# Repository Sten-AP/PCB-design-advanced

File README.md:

# PCB-design-advanced
## Ontwerpopdracht 1
Opdracht 1 is een horloge waarvan de tijd wordt weergeven met LED's. Het schema en de PCB zijn gemaakt in kicad.
De horloge bestaat voornamelijk uit 24 LED's, een ATTINY414 met bijhorende kristal, een spanningsregelaar om van 3V naar 5V te gaan, knoppen (met pullup), een mosfet voor de LED's uiten aan te schakelen, een programmeerheader (UDPI) en een knoopcelhouder.

Dit was een nieuwe manier was van het ontwerpen van een PCB omdat er nu een onderzoek gedaan moest worden. Het onderzoek van deze opdracht is niet zo goed, dit was de bedoeling van de lector om ons er van bewust te maken.

Omdat er een probleem was met de footprint van de LED's kon de eerste versie niet werken, de ATTINY programmeerde wel maar de LED's waren verkeerd. Er kon geen nieuwe meer besteld worden door tijdsgebrek dus heb ik geprobeerd om zo goed mogelijk de LED's 90 graden gedraait te monteren op een nieuwe PCB. Dit heeft gewerkt maar nu werd het programmeren een probleem. Wederom kon de ATTINY geprogrammeerd worden maar deze keer deden de LED's niet wat ik in de programmatie plaatste, deze begonnen allemaal random aan en uit te gaan. Aangezien meerdere dit probleem hadden werd er vanuitgegaan dat het probleem aan de ATTINY lag.

## Ontwerpopdracht 2
Opdracht 2 is een macropad. Ook dit schema en PCB zijn gemaakt in kicad.
De macropad bestaat voornamelijk uit 2 trimmers, 6 toetsenbordswitches en een raspberry pico W. Omdat de trimmers ingedrukt kunnen worden als knop wil dit zeggen dat er 8 knoppen zijn. Deze knoppen zijn geschakeld in een matrix en bevatten daarvoor ook de nodige diodes.

Aangezien ik nu bewust was van het nodige onderzoek heb ik een grote stap gemaakt hiermee.

Deze opdracht is volledig compleet en is verlopen zonder fouten.

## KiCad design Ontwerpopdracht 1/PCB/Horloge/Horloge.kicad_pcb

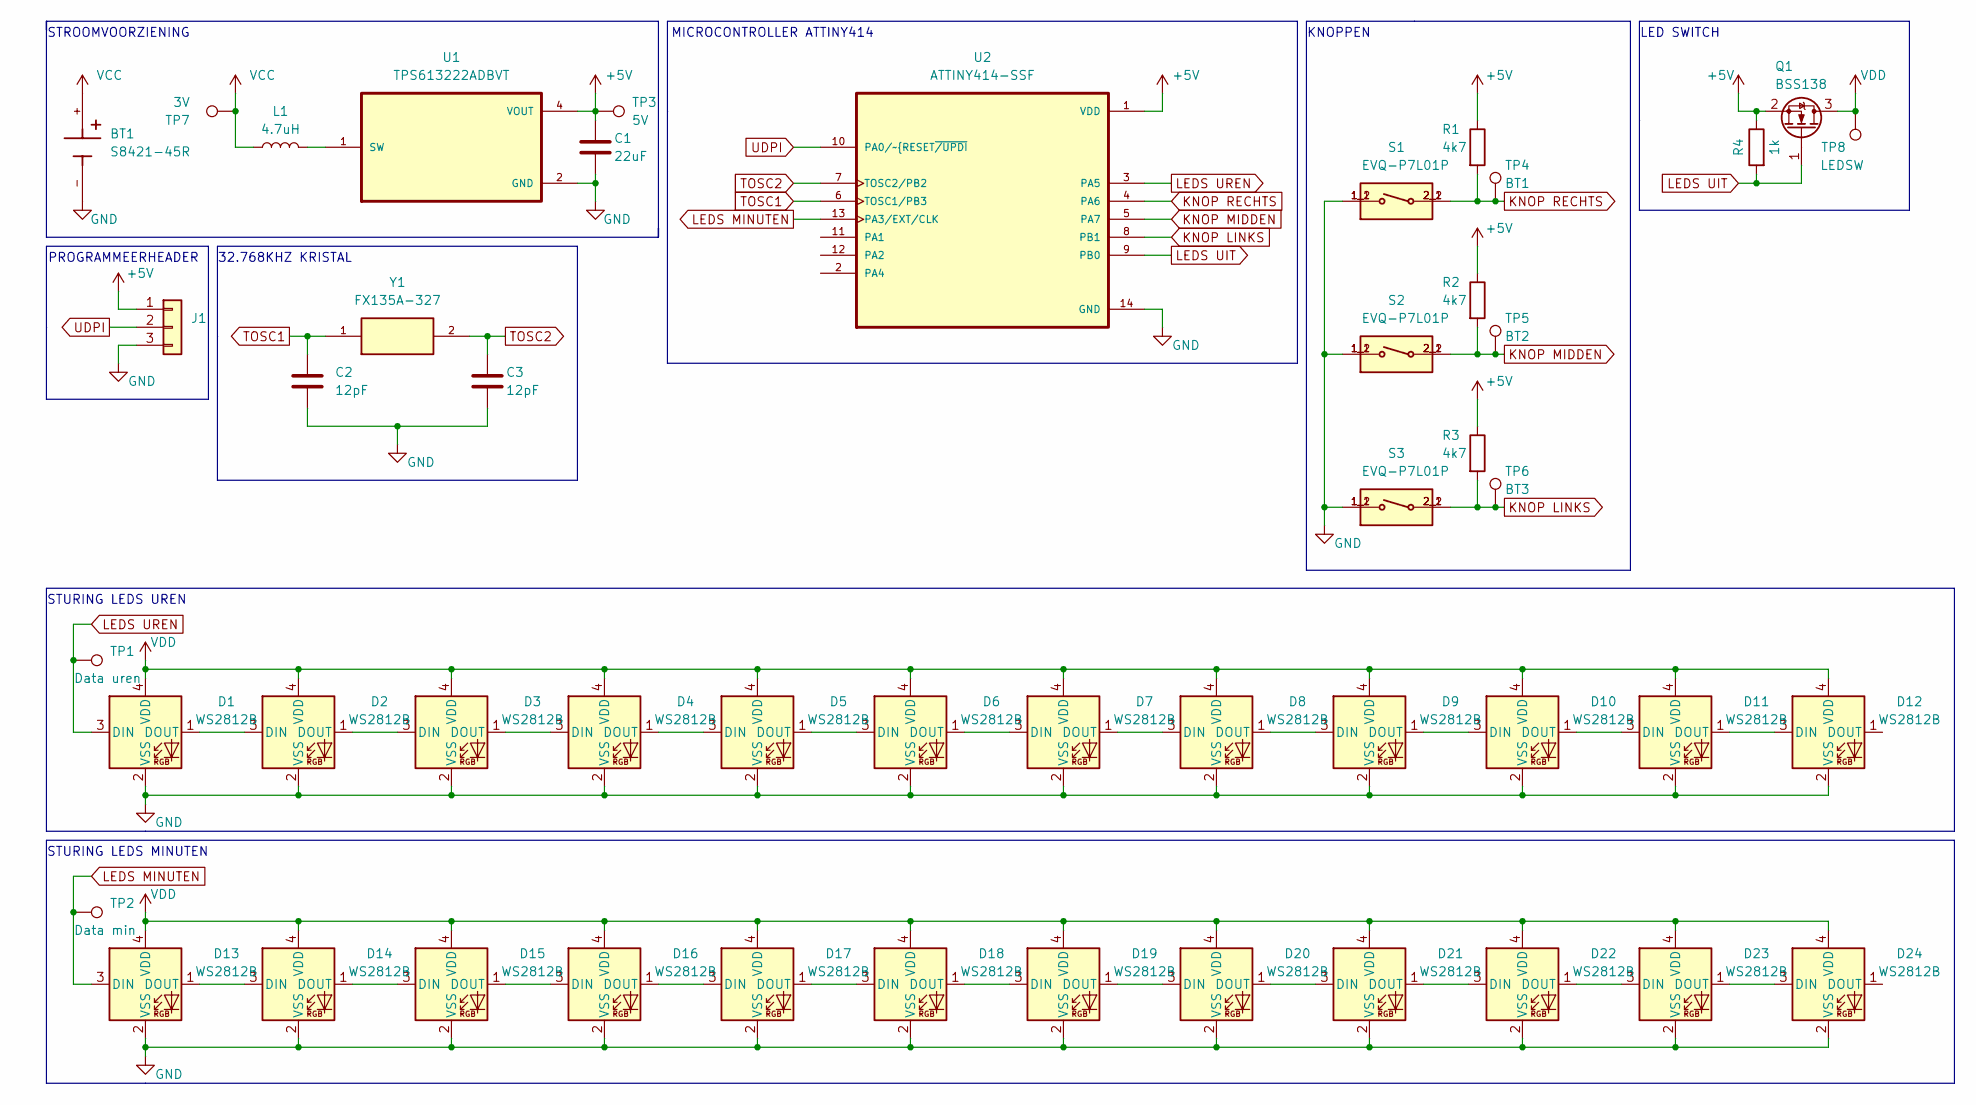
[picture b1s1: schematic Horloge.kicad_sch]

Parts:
BT1: S8421-45R; BAT_S8421-45R; PARTREV 5
C1: 22uF; C_0805_2012Metric_Pad1.18x1.45mm_HandSolder
C2, C3: 12pF; C_0805_2012Metric_Pad1.18x1.45mm_HandSolder
D1, D2, D3, D4, D5, D6, D7, D8, D9, D10, D11, D12, D13, D14, D15, D16, D17, D18, D19, D20, D21, D22, D23, D24: WS2812B; LED_WS2812B-2020_PLCC4_2.0x2.0mm
J1: Conn_01x03; PinHeader_1x03_P2.54mm_Vertical
L1: 4.7uH; L_Sunlord_SWPA5020S
Q1: BSS138; SOT-23
R1, R2, R3: 4k7; R_0805_2012Metric_Pad1.20x1.40mm_HandSolder
R4: 1k; R_0805_2012Metric_Pad1.20x1.40mm_HandSolder
S1, S2, S3: EVQ-P7L01P; SW_EVQ-P7L01P; PARTREV N/A
TP1: Data uren; TestPoint_Pad_1.5x1.5mm
TP2: Data min; TestPoint_Pad_1.5x1.5mm
TP3: 5V; TestPoint_Pad_1.5x1.5mm
TP4: BT1; TestPoint_Pad_1.5x1.5mm
TP5: BT2; TestPoint_Pad_1.5x1.5mm
TP6: BT3; TestPoint_Pad_1.5x1.5mm
TP7: 3V; TestPoint_Pad_1.5x1.5mm
TP8: LEDSW; TestPoint_Pad_1.5x1.5mm
U1: TPS613222ADBVT; SOT95P280X145-5N
U2: ATTINY414-SSF; SOIC127P600X175-14N
Y1: FX135A-327; OSCCC150X320X90-2N

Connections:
+5V: C1.1, J1.1, Q1.2 (S), R1.1, R2.1, R3.1, R4.1, TP3.1, U1.4 (VOUT), U2.1 (VDD)
GND: BT1.-, C1.2, C2.2, C3.2, D1.2 (VSS), D2.2 (VSS), D3.2 (VSS), D4.2 (VSS), D5.2 (VSS), D6.2 (VSS), D7.2 (VSS), D8.2 (VSS), D9.2 (VSS), D10.2 (VSS), D11.2 (VSS), D12.2 (VSS), D13.2 (VSS), D14.2 (VSS), D15.2 (VSS), D16.2 (VSS), D17.2 (VSS), D18.2 (VSS), D19.2 (VSS), D20.2 (VSS), D21.2 (VSS), D22.2 (VSS), D23.2 (VSS), D24.2 (VSS), J1.3, S1.1_1, S1.1_2, S2.1_1, S2.1_2, S3.1_1, S3.1_2, U1.2 (GND), U2.14 (GND)
KNOP LINKS: R3.2, S3.2_1, S3.2_2, TP6.1, U2.8 (PB1)
KNOP MIDDEN: R2.2, S2.2_1, S2.2_2, TP5.1, U2.5 (PA7)
KNOP RECHTS: R1.2, S1.2_1, S1.2_2, TP4.1, U2.4 (PA6)
LEDS MINUTEN: D13.3 (DIN), TP2.1, U2.13 (PA3/EXT/CLK)
LEDS UIT: Q1.1 (G), R4.2, U2.9 (PB0)
LEDS UREN: D1.3 (DIN), TP1.1, U2.3 (PA5)
unnamed: D1.1 (DOUT), D2.3 (DIN)
unnamed: D2.1 (DOUT), D3.3 (DIN)
unnamed: D3.1 (DOUT), D4.3 (DIN)
unnamed: D4.1 (DOUT), D5.3 (DIN)
unnamed: D5.1 (DOUT), D6.3 (DIN)
unnamed: D6.1 (DOUT), D7.3 (DIN)
unnamed: D7.1 (DOUT), D8.3 (DIN)
unnamed: D8.1 (DOUT), D9.3 (DIN)
unnamed: D9.1 (DOUT), D10.3 (DIN)
unnamed: D10.1 (DOUT), D11.3 (DIN)
unnamed: D11.1 (DOUT), D12.3 (DIN)
unnamed: D13.1 (DOUT), D14.3 (DIN)
unnamed: D14.1 (DOUT), D15.3 (DIN)
unnamed: D15.1 (DOUT), D16.3 (DIN)
unnamed: D16.1 (DOUT), D17.3 (DIN)
unnamed: D17.1 (DOUT), D18.3 (DIN)
unnamed: D18.1 (DOUT), D19.3 (DIN)
unnamed: D19.1 (DOUT), D20.3 (DIN)
unnamed: D20.1 (DOUT), D21.3 (DIN)
unnamed: D21.1 (DOUT), D22.3 (DIN)
unnamed: D22.1 (DOUT), D23.3 (DIN)
unnamed: D23.1 (DOUT), D24.3 (DIN)
unnamed: L1.2, U1.1 (SW)
TOSC1: C2.1, U2.6 (TOSC1/PB3), Y1.1
TOSC2: C3.1, U2.7 (TOSC2/PB2), Y1.2
UDPI: J1.2, U2.10 (PA0/~RESET~{/UPDI)
VCC: BT1.+, L1.1, TP7.1
VDD: D1.4 (VDD), D2.4 (VDD), D3.4 (VDD), D4.4 (VDD), D5.4 (VDD), D6.4 (VDD), D7.4 (VDD), D8.4 (VDD), D9.4 (VDD), D10.4 (VDD), D11.4 (VDD), D12.4 (VDD), D13.4 (VDD), D14.4 (VDD), D15.4 (VDD), D16.4 (VDD), D17.4 (VDD), D18.4 (VDD), D19.4 (VDD), D20.4 (VDD), D21.4 (VDD), D22.4 (VDD), D23.4 (VDD), D24.4 (VDD), Q1.3 (D), TP8.1

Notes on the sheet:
32.768KHZ KRISTAL
KNOPPEN
STURING LEDS UREN
STROOMVOORZIENING
LED SWITCH
PROGRAMMEERHEADER
STURING LEDS MINUTEN
MICROCONTROLLER ATTINY414

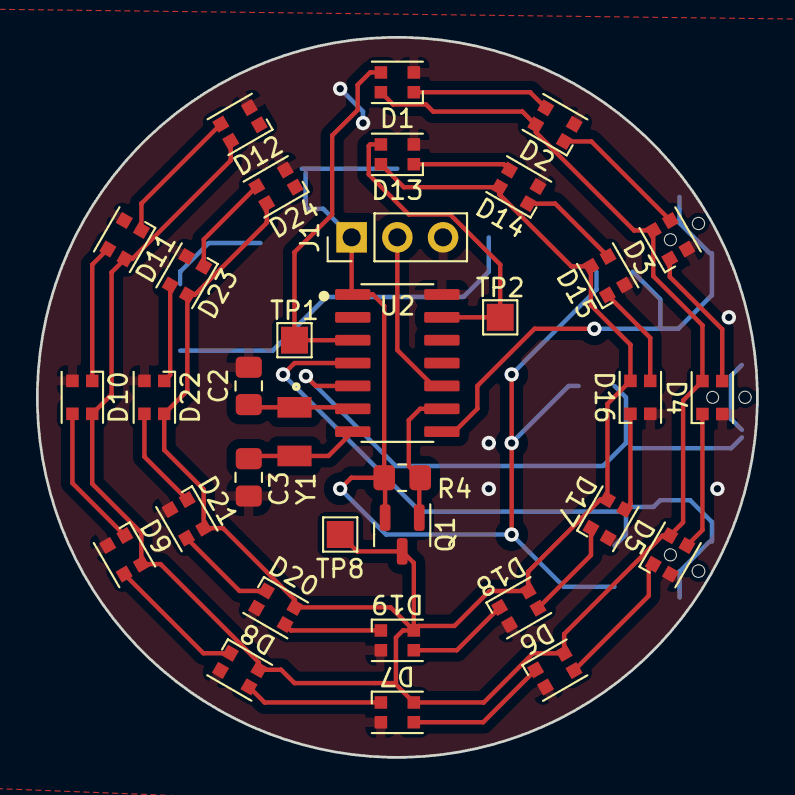
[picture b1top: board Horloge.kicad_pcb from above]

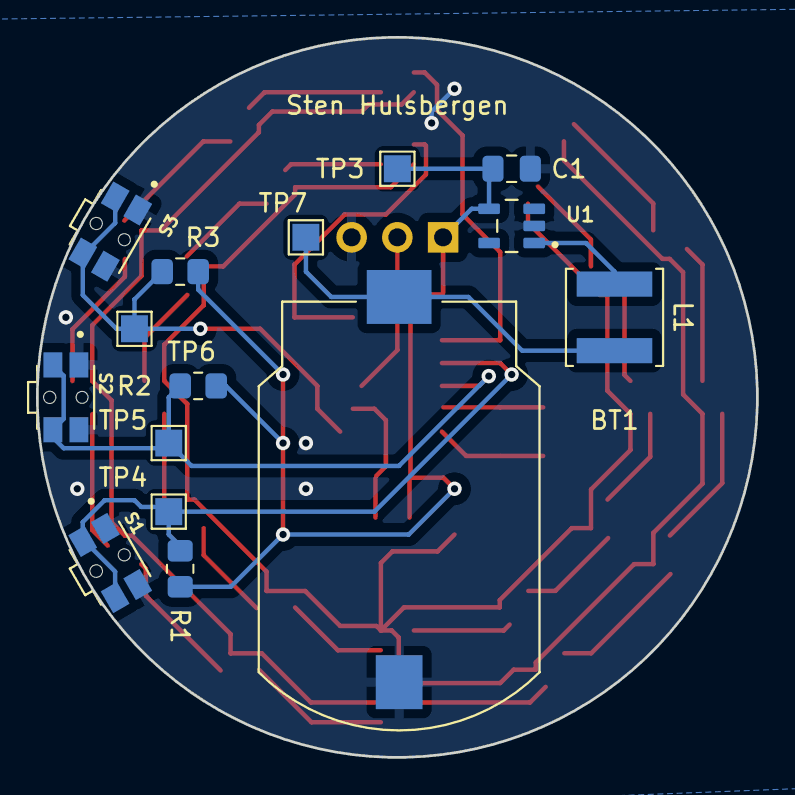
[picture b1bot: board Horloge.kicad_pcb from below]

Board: 2 copper layers, 40.0 x 40.0 mm, 49 parts (15 on the bottom side), 36 nets.

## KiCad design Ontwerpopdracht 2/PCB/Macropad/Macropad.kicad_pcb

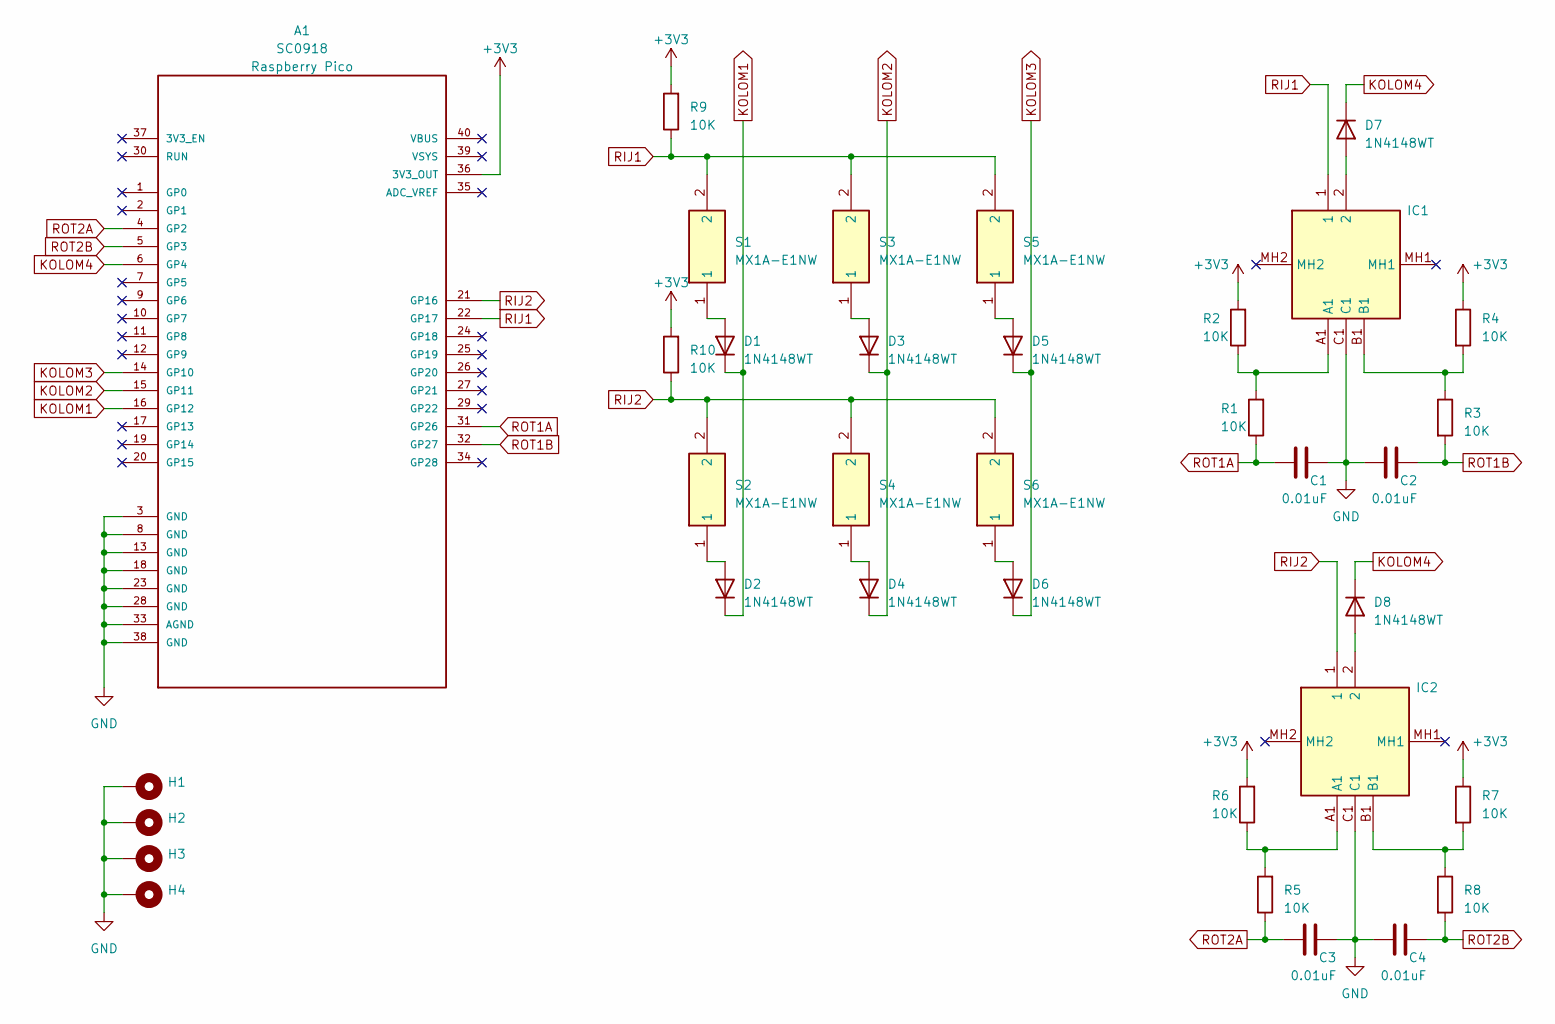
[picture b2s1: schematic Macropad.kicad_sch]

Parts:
A1: SC0918; MODULE_SC0918; PARTREV 1.6
C1, C2, C3, C4: 0.01uF; C_0805_2012Metric_Pad1.18x1.45mm_HandSolder
D1, D2, D3, D4, D5, D6, D7, D8: 1N4148WT; D_SOD-123
H1, H2, H3, H4: MountingHole_Pad; MountingHole_2.2mm_M2_Pad_Via
IC1, IC2: PEC12R-4220F-S0024; PEC12R4220FS0024; Mouser Part Number 652-PEC12R-4220F-S24
R1, R2, R3, R4, R5, R6, R7, R8, R9, R10: 10K; R_0805_2012Metric_Pad1.20x1.40mm_HandSolder
S1, S2, S3, S4, S5, S6: MX1A-E1NW; SW_Cherry_MX_1.00u_PCB; Mouser Part Number 540-MX1A-E1NW

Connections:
+3V3: A1.36 (3V3_OUT), R2.2, R4.1, R6.2, R7.1, R9.2, R10.2
GND: A1.3 (GND), A1.8 (GND), A1.13 (GND), A1.18 (GND), A1.23 (GND), A1.28 (GND), A1.33 (AGND), A1.38 (GND), C1.2, C2.1, C3.2, C4.1, H1.1, H2.1, H3.1, H4.1, IC1.C1, IC2.C1
KOLOM1: A1.16 (GP12), D1.1 (K), D2.1 (K)
KOLOM2: A1.15 (GP11), D3.1 (K), D4.1 (K)
KOLOM3: A1.14 (GP10), D5.1 (K), D6.1 (K)
KOLOM4: A1.6 (GP4), D7.1 (K), D8.1 (K)
unnamed: D1.2 (A), S1.1
unnamed: D2.2 (A), S2.1
unnamed: D3.2 (A), S3.1
unnamed: D4.2 (A), S4.1
unnamed: D5.2 (A), S5.1
unnamed: D6.2 (A), S6.1
unnamed: D7.2 (A), IC1.2
unnamed: D8.2 (A), IC2.2
unnamed: IC1.A1, R1.2, R2.1
unnamed: IC1.B1, R3.1, R4.2
unnamed: IC2.A1, R5.2, R6.1
unnamed: IC2.B1, R7.2, R8.1
RIJ1: A1.22 (GP17), IC1.1, R9.1, S1.2, S3.2, S5.2
RIJ2: A1.21 (GP16), IC2.1, R10.1, S2.2, S4.2, S6.2
ROT1A: A1.31 (GP26), C1.1, R1.1
ROT1B: A1.32 (GP27), C2.2, R3.2
ROT2A: A1.4 (GP2), C3.1, R5.1
ROT2B: A1.5 (GP3), C4.2, R8.2

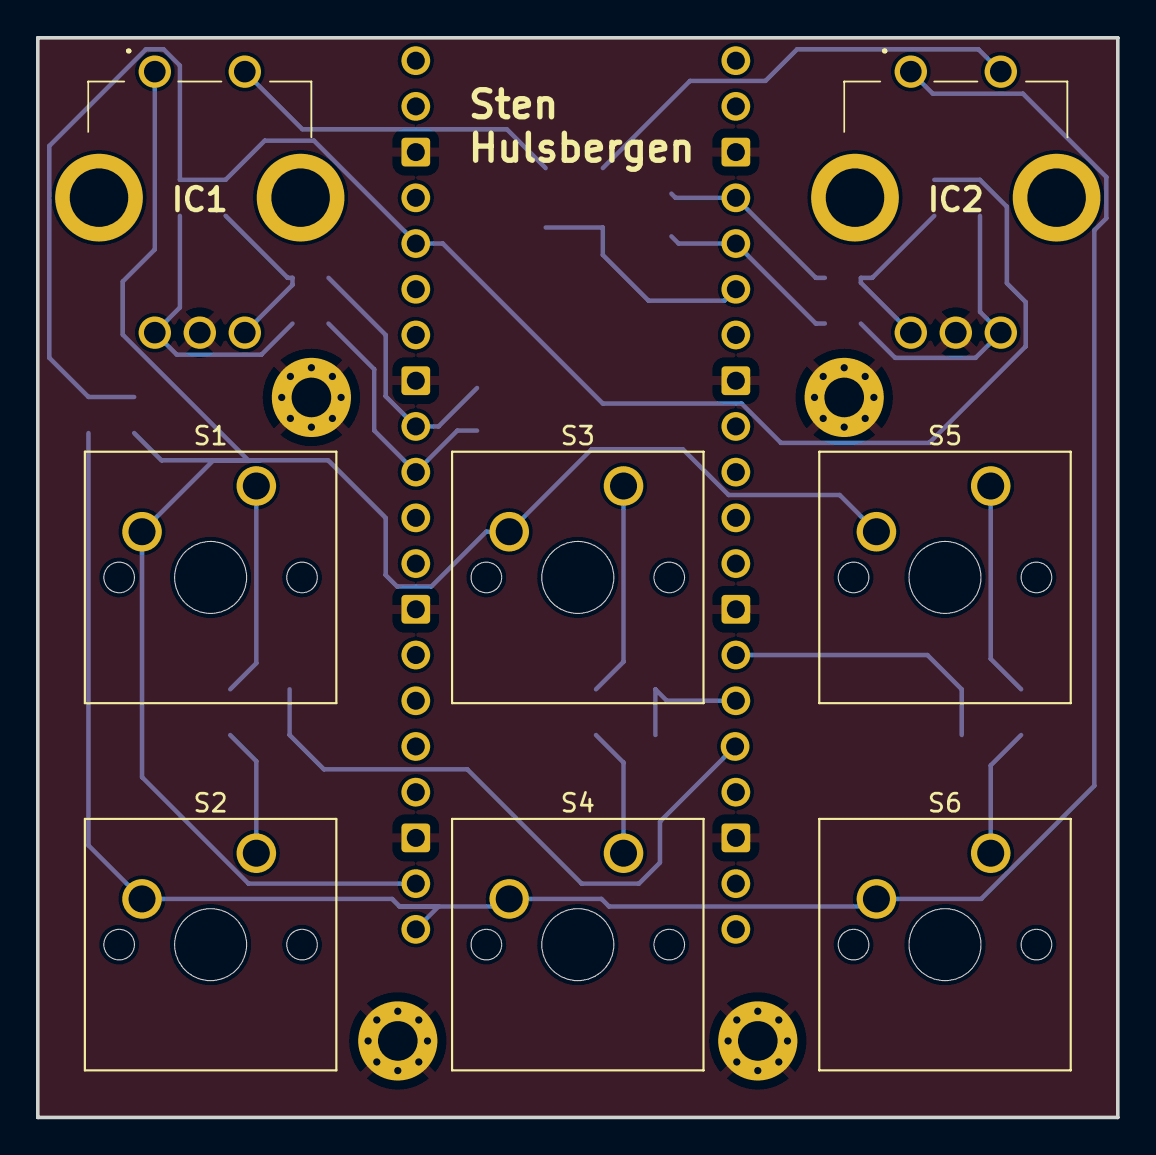
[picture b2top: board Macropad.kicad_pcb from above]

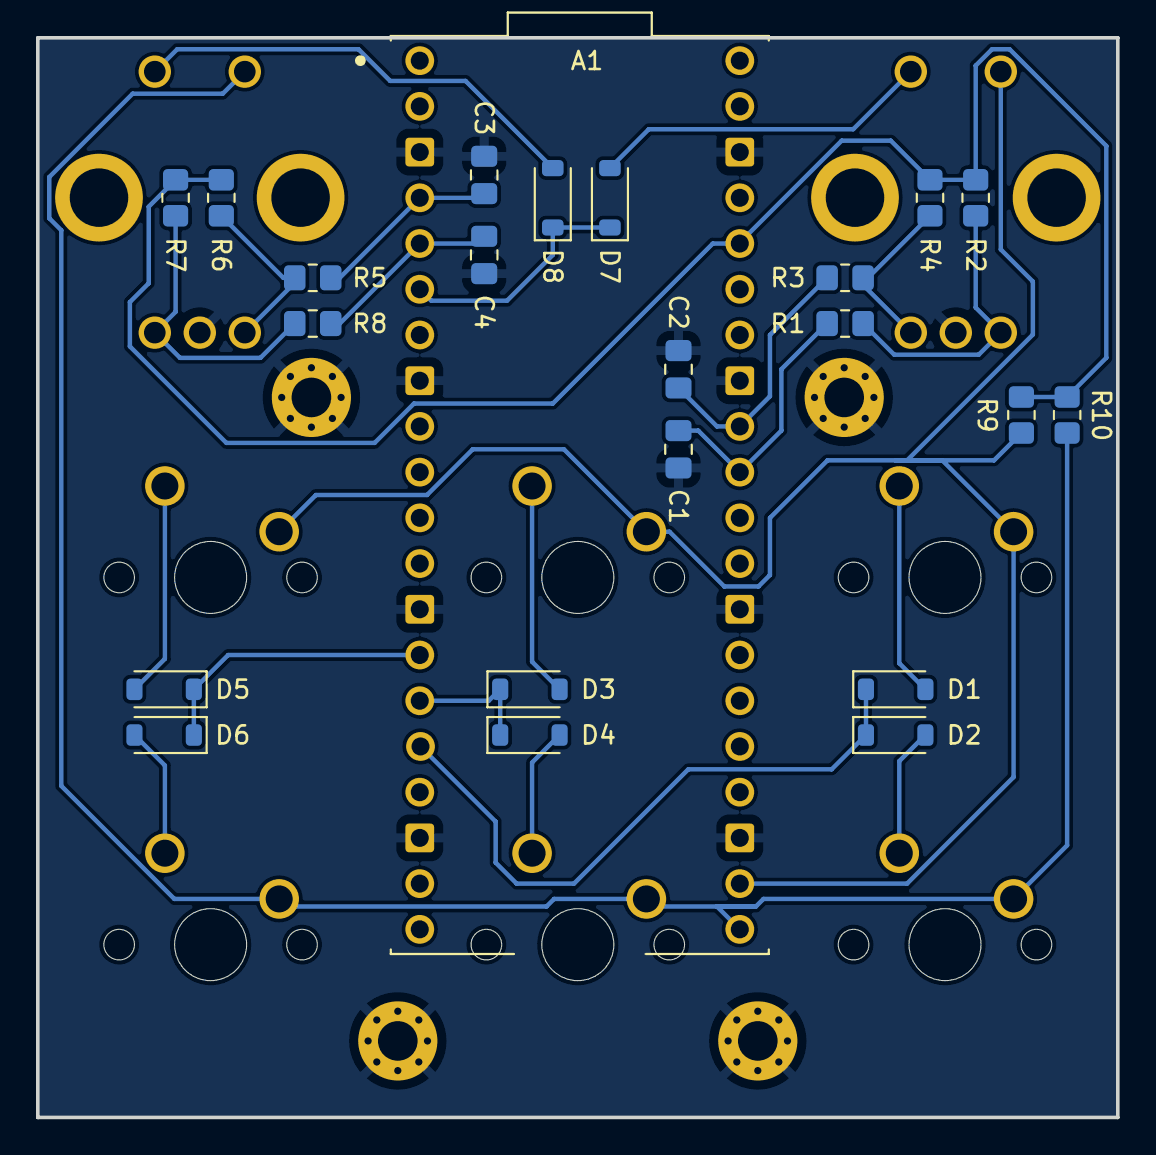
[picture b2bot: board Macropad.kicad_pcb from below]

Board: 2 copper layers, 60.0 x 60.0 mm, 35 parts (23 on the bottom side), 24 nets.

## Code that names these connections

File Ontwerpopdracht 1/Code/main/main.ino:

#include <tinyNeoPixel.h>

#define MOSFET PIN_PB0
#define LED_PIN_UREN PIN_PA5
#define LED_PIN_MINUTEN PIN_PA3
#define KNOP_RECHTS PIN_PA6
#define KNOP_MIDDEN PIN_PA7
#define KNOP_LINKS PIN_PB1

#define NUM_LEDS 12

tinyNeoPixel UREN(NUM_LEDS, LED_PIN_UREN, NEO_GRB);
tinyNeoPixel MINUTEN(NUM_LEDS, LED_PIN_MINUTEN, NEO_GRB);

void setup() {
  // Leds en mosfet initialiseren als output
  pinMode(MOSFET, OUTPUT);
  pinMode(LED_PIN_UREN, OUTPUT);
  pinMode(LED_PIN_MINUTEN, OUTPUT);

  // Knoppen initialiseren als input
  pinMode(KNOP_RECHTS, INPUT);
  pinMode(KNOP_MIDDEN, INPUT);
  pinMode(KNOP_LINKS, INPUT);

  // Mosfet aan zetten
  digitalWrite(MOSFET, HIGH); 
  UREN.begin();
}

void loop() {
  if (digitalRead(KNOP_RECHTS)) {
    UREN.clear();
    for (byte i = 0; i < NUM_LEDS; i++){
      UREN.setPixelColor(i, UREN.Color(0, 0, 255));
    }
    delay(500);
    UREN.show();
  }
  else if (digitalRead(KNOP_MIDDEN)){
    UREN.clear();
    for (byte i = 0; i < NUM_LEDS; i++){
      UREN.setPixelColor(i, UREN.Color(0, 255, 0));
    }
    delay(500);
    UREN.show();
  }
  else if (digitalRead(KNOP_LINKS)){
    UREN.clear();
    for (byte i = 0; i < NUM_LEDS; i++){
      UREN.setPixelColor(i, UREN.Color(255, 0, 0));
    }
    delay(500);
    UREN.show();
  }
}

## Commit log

2023-02-09 start
2023-02-09 kikad+doc
2023-02-09 update doc
2023-02-10 aanpassing doc
2023-02-12 documentatie klaar
2023-02-12 update schema
2023-02-16 schema
2023-02-16 update schema + doc scema
2023-02-16 aanpassing attiny, update doc schema
2023-02-26 aanpassing schema
2023-03-02 batterijhouder + pcb + schema
2023-03-03 pcb klaar
2023-03-08 pcb af
2023-03-16 pcb finaal + code
2023-03-23 testcode
2023-03-31 horloge klaar
2023-04-19 doc klaar
2023-04-20 start design pcb
2023-04-27 pcb doc klaar
2023-05-04 programatie
2023-05-08 verschillende librarys geprobeerd
2023-05-11 pcb macropad klaar
2023-05-11 knoppen en rotary werken
2023-05-12 code macropad klaar
2023-05-27 code
2023-05-31 finale code
2023-06-05 documentatie, foto's, etc
2023-06-08 eindresultaat horloge
